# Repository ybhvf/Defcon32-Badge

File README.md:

```
 ______      _____
|__  (_) __ |_   _| __ ___  _ __
  / /| |/ _` || || '__/ _ \| '_ \
 / /_| | (_| || || | | (_) | | | |
/____|_|\__,_||_||_|  \___/|_| |_|
----------------------------------
D C Z I A  --------------  2 0 2 4
```

# About
Introducing the 2024 DCZia Badge - The Ziatron
1.9" of full-color LCD goodness. One knob to rule them all. A mic, _and_ a speaker! Full color dye sub panel art. Up to 18 full color LEDs! Software that does stuff, and or things*!

\* please note things may not be avaliable in all markerts, subject to avalibility, not valid in New Jersey, may contain traces of nuts, please consult your doctor before using any DCZia product.

# Specs
LCD Screen

Raspberry Pi Pico W, now with added WiFi!

One rotary encoder, with click function. Spared no expsense!

Micro Mechanical Microphone, by TDK!

0.3"? Speaker!

Powered by not one, not two, but three, _three_ AAA batteries! Endless Power! (\* please note power is not infact endless.)

# Build Guide
If you need to teardown the badge, please see the full BuildGuide.md in the repo. For defcon badges, you will need to add the rotary encoder, battery pack, and flash the firmware.

First put the rotary encoder through the hole on the front of they board. Solder on all the pins and stabilization tabs on the back of the board. Then remove the double sticky tape and secure the battery pack to the board. Next solder the black wire of the battery pack to the negative pad on the back of the board, and the red to the positive.

If you start up the badge with the shipped firmware you should get a test mode to see if everything works. To flash our initial full fimrware, use a non conductive tool to push the white button on the board of the Raspberry pi Pico, and plug it into your computer. A USB Mass storage device should appear. Download the single u2f file from the release section of our github, and drag it onto the drive. The board should then reboot when the transfer is done and you should have a badge!

The initial firmware has a mode with light patterns, a sound reactive "rave" light mode (the knob will control the sensitivity of the microphone), and can show raw formatted images off a SD card. We wanted to implement a SSTV encode and decode, but did not finish in time for con. If you wish to hack on this and submit a PR go for it! 

# Recommended IDEs
A commodore 64 with a serial to micro USB adapter. If not avaliable, we recommend Visual Studio Code with the MicroPico extension, or the Thonny IDE.

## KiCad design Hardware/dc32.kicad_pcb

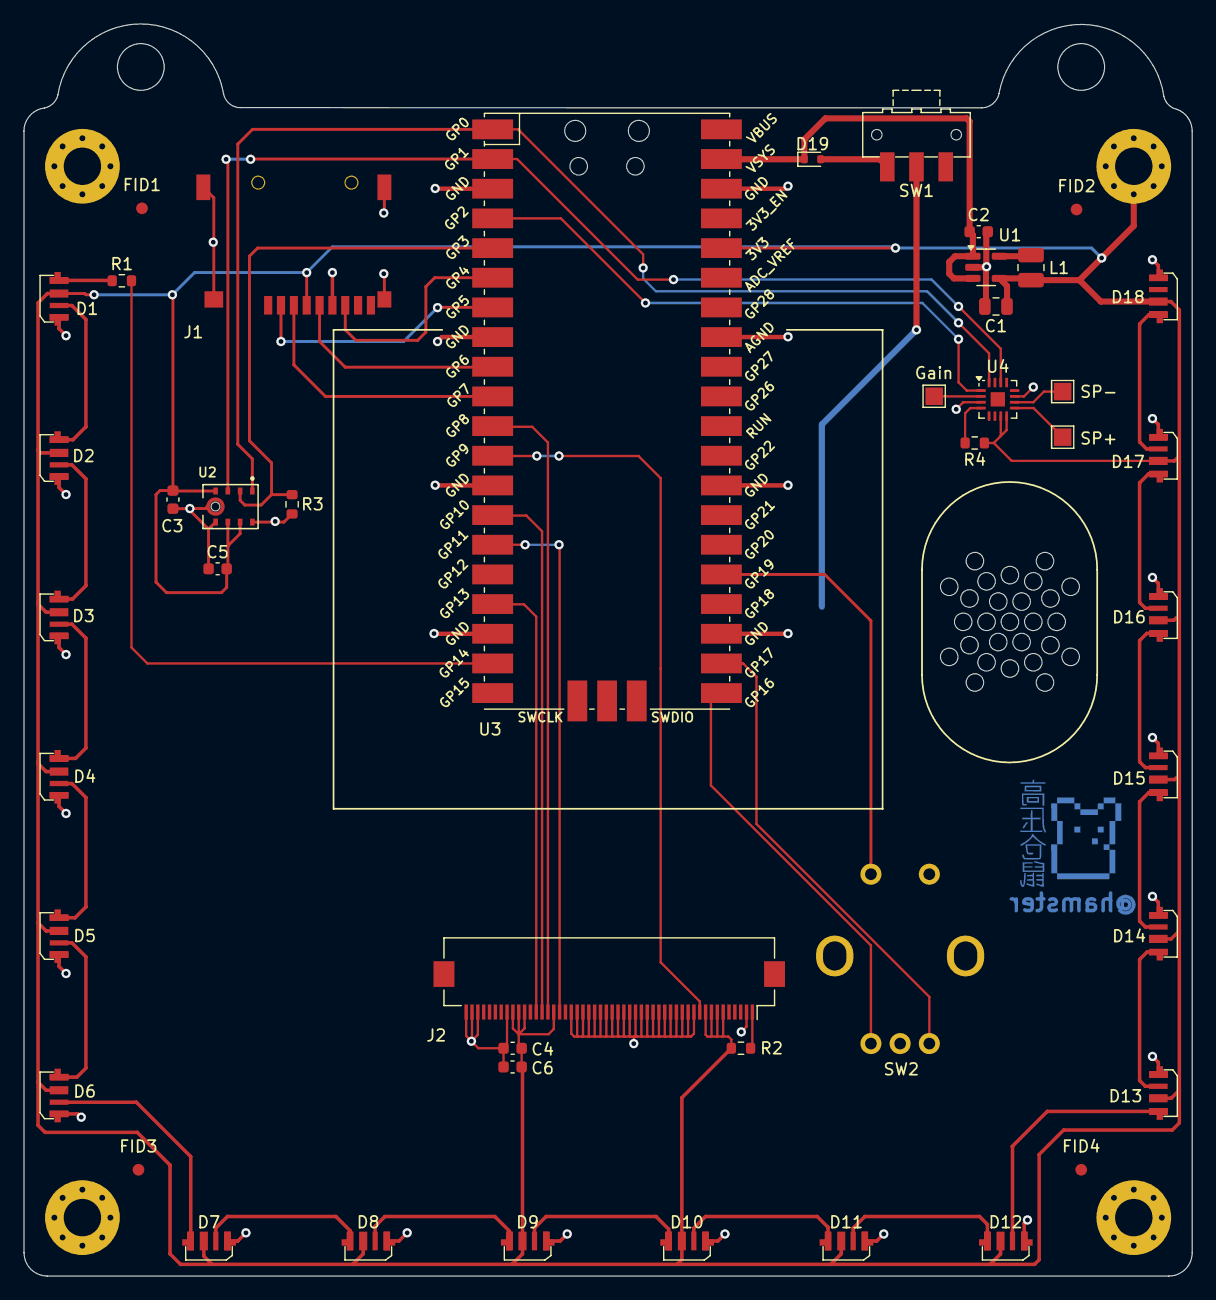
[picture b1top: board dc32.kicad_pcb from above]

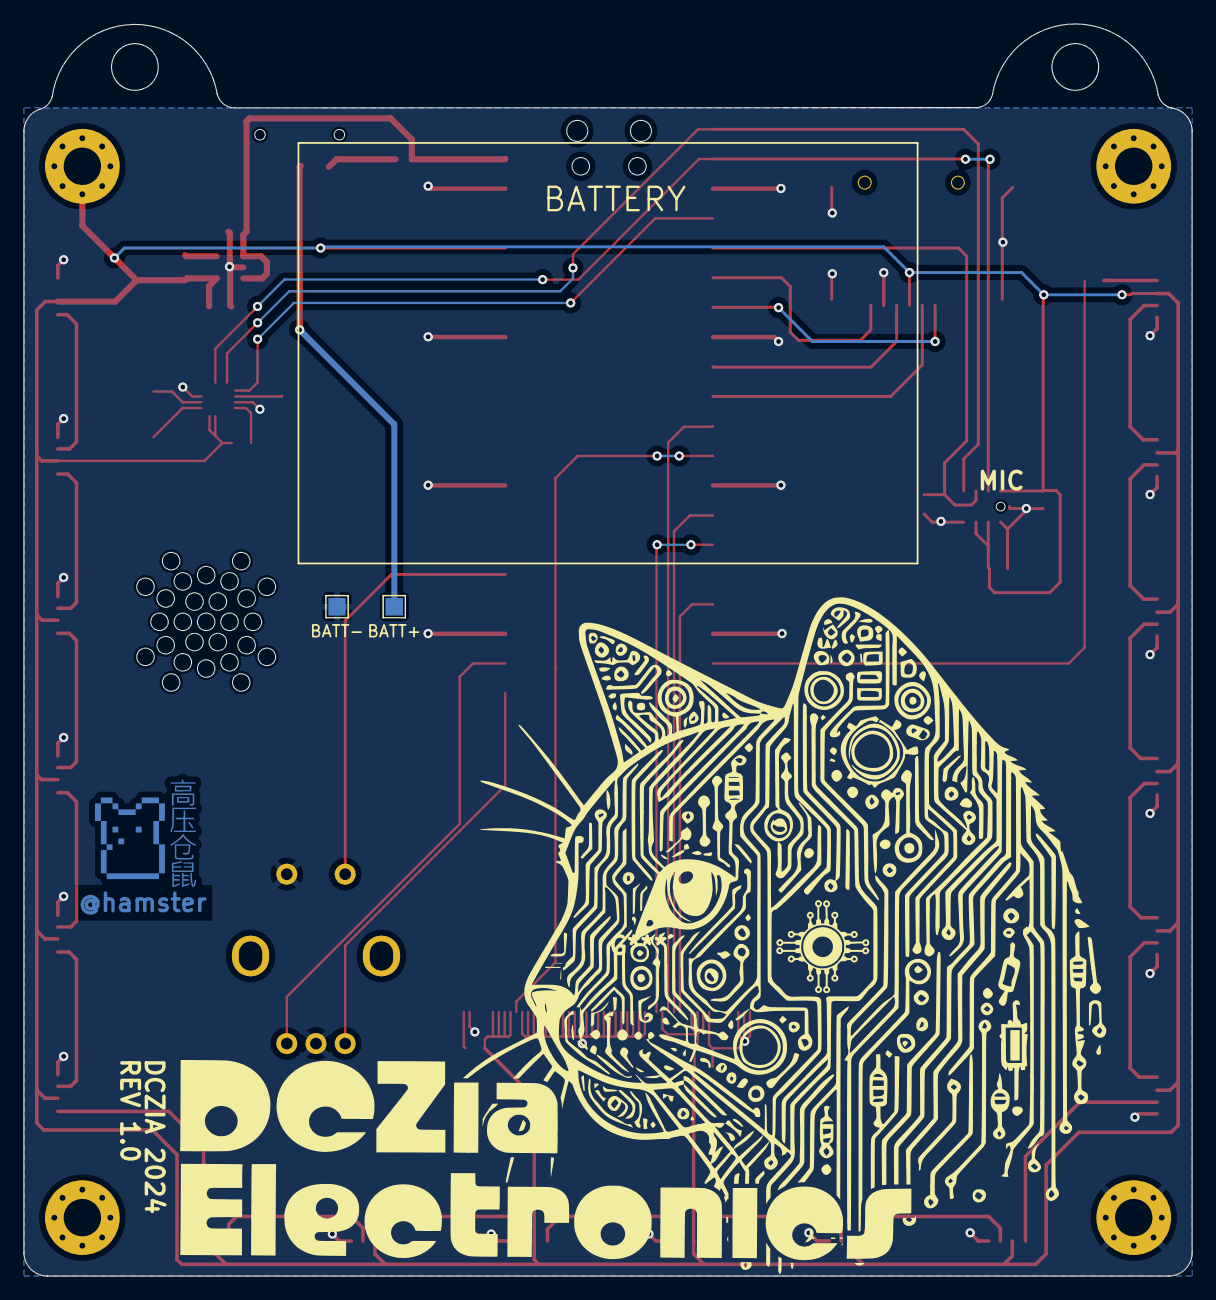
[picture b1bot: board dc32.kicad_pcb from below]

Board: 2 copper layers, 100.0 x 107.2 mm, 51 parts (6 on the bottom side), 46 nets.

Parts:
C1: 22uF; C_0805_2012Metric
C2, C6: 10uF; C_0603_1608Metric
C3, C4, C5: 0.1uF; C_0603_1608Metric
D1, D2, D3, D4, D5, D6, D7, D8, D9, D10, D11, D12, D13, D14, D15, D16, D17, D18: WS2812B; LED_SK6812_4020
D19: D_Schottky; D_SOD-523
FID1, FID2, FID3, FID4: Fiducial; Fiducial_1mm_Mask2mm
H1: Top Right; MountingHole_3.2mm_M3_Pad_Via
H2: Top Left; MountingHole_3.2mm_M3_Pad_Via
H3: Bottom Right; MountingHole_3.2mm_M3_Pad_Via
H4: Bottom Left; MountingHole_3.2mm_M3_Pad_Via
J1: Micro_SD_Card_SPI; MicroSD-Socket-Seeed-320090008
J2: Conn_01x50; Hirose_FH12-50S-0.5SH_1x50-1MP_P0.50mm_Horizontal
L1: 1uH; L_1008_2520Metric
R1: 10R; R_0603_1608Metric
R2: 33R; R_0603_1608Metric
R3: 100k; R_0603_1608Metric
R4: 1M; R_0603_1608Metric
SW1: SW_SPDT; SW_SPDT_CK-JS102011SAQN
SW2: Function Select; RotaryEncoder
TP1: BATT+; TestPoint_Pad_1.5x1.5mm
TP2: BATT-; TestPoint_Pad_1.5x1.5mm
TP3: Gain; TestPoint_Pad_1.5x1.5mm
TP4: SP-; TestPoint_Pad_1.5x1.5mm
TP5: SP+; TestPoint_Pad_1.5x1.5mm
U1: SC189ZULTRT; SOT-23-5
U2: INMP4441; MIC_INMP441ACEZ-R7
U3: Pico; RPi_Pico_SMD
U4: MAX98357A/B; TQFN-16-1EP_3x3mm_P0.5mm_EP1.23x1.23mm

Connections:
+3V3: C1.1, C3.2, C4.2, C5.2, C6.2, D1.2 (VDD), D2.2 (VDD), D3.2 (VDD), D4.2 (VDD), D5.2 (VDD), D6.2 (VDD), D7.2 (VDD), D8.2 (VDD), D9.2 (VDD), D10.2 (VDD), D11.2 (VDD), D12.2 (VDD), D13.2 (VDD), D14.2 (VDD), D15.2 (VDD), D16.2 (VDD), D17.2 (VDD), D18.2 (VDD), H1.1, J1.4 (VDD), J2.6, J2.7, J2.8, J2.9, J2.35, J2.40, J2.41, J2.42, L1.2, R2.1, R4.1, U1.4 (OUT), U2.4 (L/R), U2.7 (Vdd), U2.8 (CHIPEN), U3.36 (3V3), U4.7 (Vdd), U4.8 (Vdd)
ENC1_A: SW2.A, U3.21 (GPIO16)
ENC1_B: SW2.B, U3.22 (GPIO17)
ENC1_SW: SW2.S1, U3.25 (GPIO19)
GND: C1.2, C2.2, C3.1, C4.1, C5.1, C6.1, D1.4 (VSS), D2.4 (VSS), D3.4 (VSS), D4.4 (VSS), D5.4 (VSS), D6.4 (VSS), D7.4 (VSS), D8.4 (VSS), D9.4 (VSS), D10.4 (VSS), D11.4 (VSS), D12.4 (VSS), D13.4 (VSS), D14.4 (VSS), D15.4 (VSS), D16.4 (VSS), D17.4 (VSS), D18.4 (VSS), H4.1, J1.6 (VSS), J1.10 (SHIELD), J2.2, J2.11, J2.12, J2.13, J2.14, J2.15, J2.16, J2.17, J2.18, J2.19, J2.20, J2.21, J2.22, J2.23, J2.24, J2.25, J2.26, J2.27, J2.28, J2.29, J2.30, J2.31, J2.32, J2.43, J2.48, J2.49, J2.50, R3.2, SW2.C, SW2.S2, TP2.1, U1.2 (GND), U2.5 (GND), U2.6 (GND), U2.9 (GND), U3.3 (GND), U3.8 (GND), U3.13 (GND), U3.18 (GND), U3.23 (GND), U3.28 (GND), U3.33 (AGND), U3.38 (GND), U4.3 (GND), U4.11 (GND)
I2S_BCLK: U2.1 (SCK), U3.1 (GPIO0), U4.16 (BCLK)
I2S_DIN: U3.4 (GPIO2), U4.1 (DIN)
I2S_DOUT: R3.1, U2.2 (SD), U3.5 (GPIO3)
I2S_LRCLK: U2.3 (WS), U3.2 (GPIO1), U4.14 (LRCLK)
LCD_CS: J2.38, U3.17 (GPIO13)
LCD_DC: J2.36, U3.11 (GPIO8)
LCD_RESET: J2.10, U3.12 (GPIO9)
unnamed: D1.1 (DIN), R1.1
unnamed: D1.3 (DOUT), D2.1 (DIN)
unnamed: D2.3 (DOUT), D3.1 (DIN)
unnamed: D3.3 (DOUT), D4.1 (DIN)
unnamed: D4.3 (DOUT), D5.1 (DIN)
unnamed: D5.3 (DOUT), D6.1 (DIN)
unnamed: D6.3 (DOUT), D7.1 (DIN)
unnamed: D7.3 (DOUT), D8.1 (DIN)
unnamed: D8.3 (DOUT), D9.1 (DIN)
unnamed: D9.3 (DOUT), D10.1 (DIN)
unnamed: D10.3 (DOUT), D11.1 (DIN)
unnamed: D11.3 (DOUT), D12.1 (DIN)
unnamed: D12.3 (DOUT), D13.1 (DIN)
unnamed: D13.3 (DOUT), D14.1 (DIN)
unnamed: D14.3 (DOUT), D15.1 (DIN)
unnamed: D15.3 (DOUT), D16.1 (DIN)
unnamed: D16.3 (DOUT), D17.1 (DIN)
unnamed: D17.3 (DOUT), D18.1 (DIN)
unnamed: D19.2 (A), SW1.3 (C)
unnamed: J2.1, R2.2
unnamed: SW1.2 (B), TP1.1
unnamed: L1.1, U1.5 (LX)
unnamed: TP3.1, U4.2 (GAIN_SLOT)
unnamed: TP4.1, U4.10 (OUTN)
unnamed: TP5.1, U4.9 (OUTP)
unnamed: R4.2, U4.4 (~SD_MODE)
RGB: R1.2, U3.19 (GPIO14)
SD_CS: J1.2 (/CS), U3.7 (GPIO5)
SPI0_MISO: J1.7 (DO), U3.6 (GPIO4)
SPI0_MOSI: J1.3 (DI), U3.10 (GPIO7)
SPI0_SCK: J1.5 (CLK), U3.9 (GPIO6)
SPI1_MOSI: J2.34, U3.15 (GPIO11)
SPI1_SCK: J2.37, U3.14 (GPIO10)
VCC: C2.1, D19.1 (K), U1.1 (Vin), U1.3 (EN), U3.39 (VSYS)

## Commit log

2024-05-20 Initial checking, fleshing out mechanical design
2024-06-11 6 LEDs around the sides and bottom, 18 total. Extra 3.3v regulator on the board to supply the RGB LEDs with extra current. Assumption is at 5v each RGB LED could pull up to 50mA, though we are poweri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
2024-06-15 Cleaning schematic, ERC, making sure all footprints are in place
2024-06-20 Updated PCBs to rev 1.0 and ordered them
2024-06-26 Updated BOM
2024-07-01 Updated output files to fix pico paste layer
2024-07-07 Add template for software
2024-07-07 Add initial set of libraries
2024-07-07 Removing sequencer code
2024-07-07 Updating libraries to circuit python 9 compatible libraries
2024-07-07 Removing depricated display.show() calls
2024-07-07 Comment out mic initialization and correct syntax for displaying text
2024-07-07 Corrected display pinout (hopefully)
2024-07-07 Fixing my comment fail and setting mic pins
2024-07-08 Slight changes to allow the program to boot
2024-07-08 Fixed display mirroring in a hacky way
2024-07-12 Adding audio out test to SSTV Encode section
2024-07-13 Add display image test
2024-07-13 Removing some test code that slipped in
2024-07-16 Restructure directories and add micropython build
2024-07-18 Adding STLs Updating BOM
2024-07-19 Move everything to modules
2024-07-20 Prevent crash on boot without SD card inserted
2024-07-20 Chile Pulse Animation
2024-07-20 Rainbow and Rainbow Chase animations
2024-07-21 Make menu faster by avoiding full refresh.
2024-07-21 Menu edge-case fix and removing debug prints
2024-07-21 Add small wait when entering a new state to avoid bouncing
2024-07-21 Add a state that varies brightness by audio intensity.
2024-07-22 Make animations run of ticks instead of using sleeps
2024-07-23 Add menu to party mode, and move menu functions to their own file
2024-07-23 Wav playback example added
2024-07-25 Adding unoptimized sstv encode
2024-07-26 Add code for hardware test (not called from main yet)
2024-07-26 Add encoder tests to hardware test
2024-07-27 Add sound reactive rave mode
2024-07-28 adding gitignore
2024-07-28 model and stl file
2024-07-29 more models
2024-07-29 Add hardware test uf2
2024-07-31 Č̶͔̣̼̝̅̉͗̈́͂̃ř̴̨̧̩̗̝͇̻͚̝͔̣̭͍͘͜͜e̶̢̹͖̮͓͚͌̆̓͊̏̂̐̈́̍͑̈́͛̅̈̍͐͜ä̴̱̙̟͕͂̀̂̎̄̄̆̆̓̕ṫ̷̟͎̾̔̋̓̈́͊̀̚͝e̶̺̱̥̱̊̾͑͑́͐͌̾̾̄̈͜ ̸̡̲͙͙̜͇͓̪̝͎͍̦͚͚̔̈́̈̐̓̄̾̇̍̊́́͌̋͐͜R̶̡͖̼͚̓̉͒͆̂̀̊̏̇̓͗̌́̏͠͠͝E̴̛̞͎͖̟̐̈́͑͑̀̇͛̚͝A̷̳̗̺̗̖͍͍͛̒̆D̵̨̫̊̋̋̕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
    A̷̢̛͉̲͈̩̩͗̉́̑̀̔̓͋̽̑̓̿̃̈́̑̎d̵̛̻̿̏̍
2024-08-01 Add volume adjuster to rave state
2024-08-01 Add image picker menu
2024-08-01 Update menu.py
    Massive updates and nearly complete overhall of UI and main menu. Did not test change, just pushed to live from the web interface. #yolo
2024-08-01 Create BuildGuide.md
    git gud @ badgin guide
2024-08-01 Fix sd card image folder stuff
2024-08-01 Menu picker fix for large menus
2024-08-01 removed bezel and cleaned up for faster printing
2024-08-05 Update README.md
    un fucked formatting
2024-08-09 Add fat firmware with files
2024-08-16 Rough draft for SSTV decoding
2024-08-17 Reduce memo usage of SSTV decoder
2024-08-26 mvp for sstv decode
2024-08-26 Get opportunistic sync working
2024-08-28 Rough draft for scottie/martin modes
2024-09-18 Lots of work on sstv decoding
2024-09-18 Tweak parameters for syncing
2024-09-18 Ensure that image wraps correctly
2024-09-18 Save decoded sstv to sdcard
